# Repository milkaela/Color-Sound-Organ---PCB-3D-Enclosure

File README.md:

# Color Sound Organ: PCB-3D-Enclosure
This project contains a complete design for a **sound-reactive light organ** with 3 channels (bass, mid, treble), using a PCB designed in KiCad and a custom 3D-printed case modeled in FreeCAD.
It is intended as a simple analog project for beginners or hobbyists who want to create visual effects based on audio input.

## 📦 Files Included

| File | Description |
|------|-------------|
| `3leduri.kicad_pcb` | PCB layout for the sound organ |
| `3leduri.kicad_sch` | Schematic diagram (circuit design) |
| `3leduri.kicad_pro` | KiCad project file |
| `3leduri.kicad_prl` | Layout view settings |
| `3leduri.xml`       | Netlist and BOM data export |
| `3leduri_bom_.csv`  | Bill of materials (CSV format) |
| `3leduri_bom_.xlsx` | Bill of materials (Excel format) |
| `fp-info-cache`     | Footprint cache used by KiCad |
| `cutie2.1.FCStd`    | 3D model of the custom case (FreeCAD format) |
---

## 🧠 Functional Description

The circuit detects three different frequency bands from an audio signal (low, mid, and high), and lights up a dedicated LED for each band accordingly.

- **Low frequencies (bass)** → LED 1
- **Mid frequencies** → LED 2
- **High frequencies (treble)** → LED 3

The PCB is designed to fit perfectly into the custom enclosure, with holes for LEDs and power input.

---

## 🛠 Tools and Technologies

- **KiCad** – for PCB design
- **FreeCAD** – for designing the case
- **3D Printer** – to fabricate the enclosure
- (Optional) **Audio signal source** – via jack, aux, or microphone

---

## 🖨️ 3D Printing Information

- Format: `.FCStd` (native FreeCAD file)
- Recommended slicer: Cura, PrusaSlicer, etc.
- Material: PLA or PETG
- Print time: ~2 hours
- No supports required

---

## ⚡ Usage & Testing

1. Assemble the circuit and solder components on the PCB
2. Insert the board into the 3D-printed case
3. Connect audio input (e.g. from your phone or laptop)
4. Play music — the 3 LEDs will respond to the audio spectrum

---

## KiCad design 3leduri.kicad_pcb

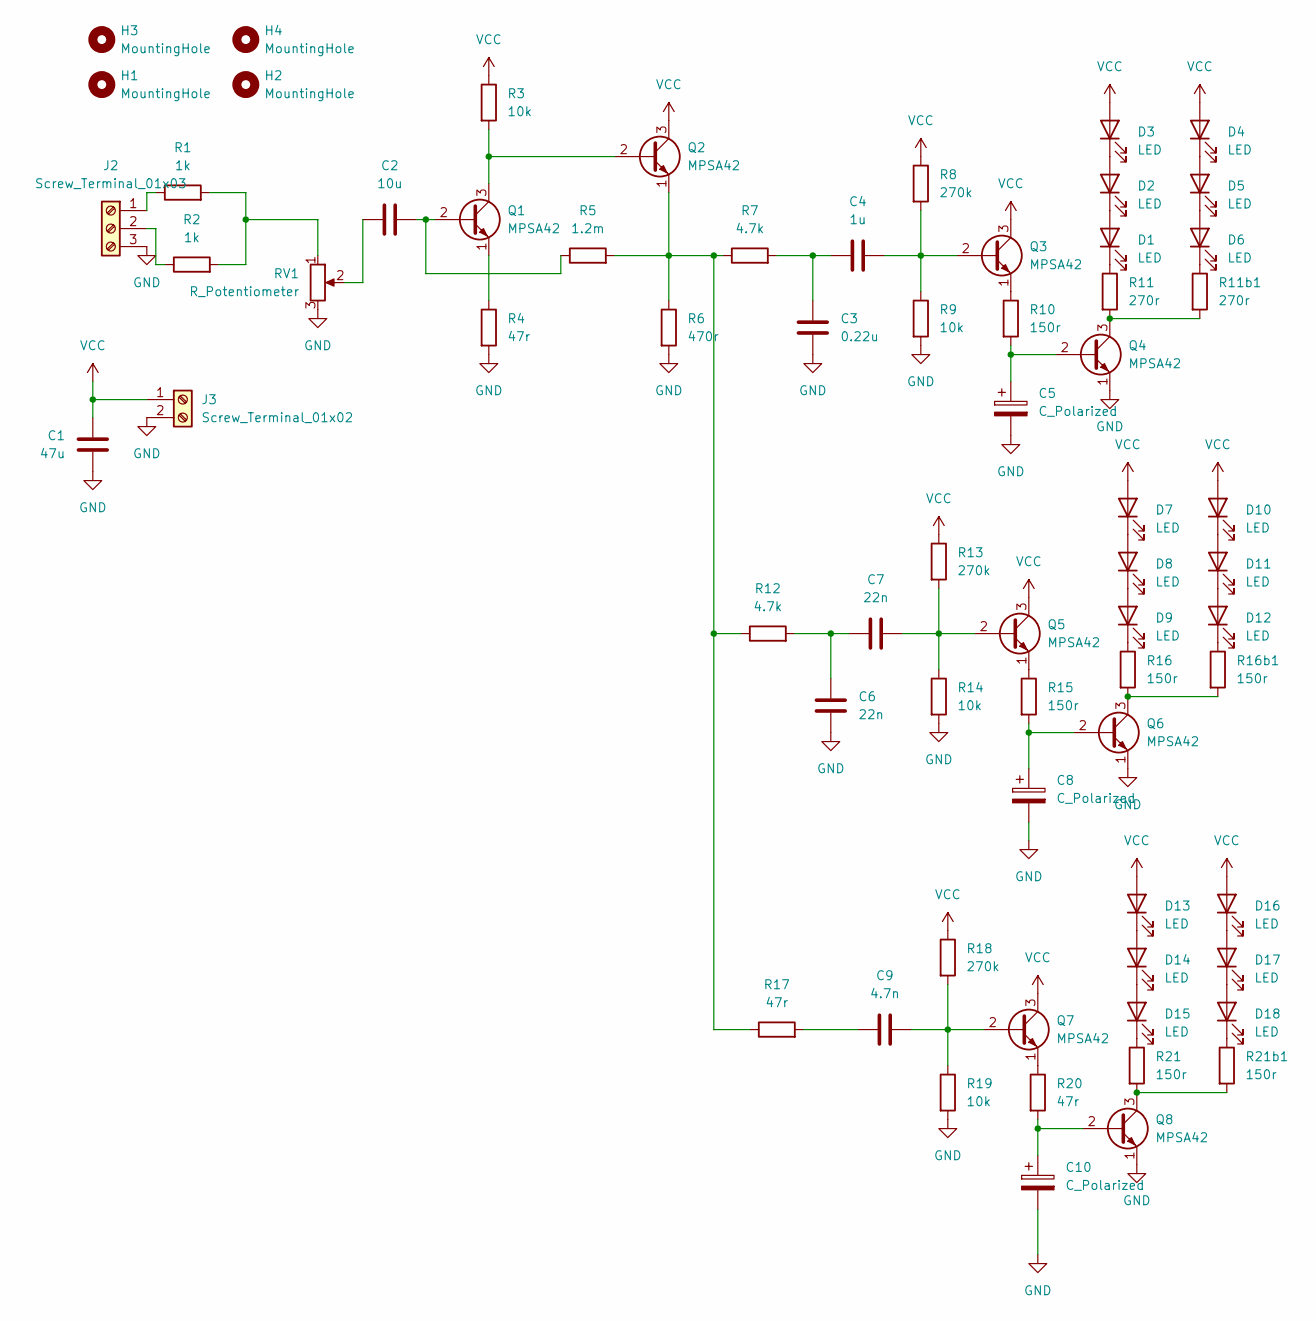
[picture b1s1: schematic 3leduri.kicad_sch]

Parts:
C1: 47u; C_1206_3216Metric_Pad1.33x1.80mm_HandSolder; mfr.part.no GCJ31CD70G476ME01L
C2: 10u; C_1206_3216Metric_Pad1.33x1.80mm_HandSolder; mfr.part.no GRM31MR61A106KE19L
C3: 0.22u; C_1206_3216Metric_Pad1.33x1.80mm_HandSolder; mfr.part.no GRM31C5C1H224JE02L
C4: 1u; C_1206_3216Metric_Pad1.33x1.80mm_HandSolder; mfr.part.no GCM31CR71H105KA55L
C5, C8, C10: C_Polarized; C_1206_3216Metric_Pad1.33x1.80mm_HandSolder
C6, C7: 22n; C_1206_3216Metric_Pad1.33x1.80mm_HandSolder; mfr.part.no GRM31BR72E223KW01L
C9: 4.7n; C_1206_3216Metric_Pad1.33x1.80mm_HandSolder; mfr.part.no GRM31CR72E473KW03L
D1, D2, D3, D4, D5, D6, D7, D8, D9, D10, D11, D12, D13, D14, D15, D16, D17, D18: LED; LED_D5.0mm; mfr.part.no MTE1201C1
H1, H2, H3, H4: MountingHole; MountingHole_3.2mm_M3
J2: Screw_Terminal_01x03; TerminalBlock_Phoenix_MKDS-1,5-3_1x03_P5.00mm_Horizontal
J3: Screw_Terminal_01x02; TerminalBlock_Phoenix_MKDS-1,5-2_1x02_P5.00mm_Horizontal; mfr.part.no 1732386
Q1, Q2, Q3, Q4, Q5, Q6, Q7, Q8: MPSA42; TO-92_Inline; mfr.part.no MPSA42
R1, R2: 1k; R_1206_3216Metric_Pad1.30x1.75mm_HandSolder; mfr.part.no RV1206JR-071KL
R3, R9, R14, R19: 10k; R_1206_3216Metric_Pad1.30x1.75mm_HandSolder; mfr.part.no ERJ-U08J103V
R4, R17, R20: 47r; R_1206_3216Metric_Pad1.30x1.75mm_HandSolder; mfr.part.no SR1206JR-1347RL
R5: 1.2m; R_1206_3216Metric_Pad1.30x1.75mm_HandSolder; mfr.part.no AC1206JR-071M2L
R6: 470r; R_1206_3216Metric_Pad1.30x1.75mm_HandSolder; mfr.part.no SR1206KR-7W470RL
R7, R12: 4.7k; R_1206_3216Metric_Pad1.30x1.75mm_HandSolder; mfr.part.no AR1206JR-074K7L
R8, R13, R18: 270k; R_1206_3216Metric_Pad1.30x1.75mm_HandSolder; mfr.part.no AF1206JR-07270KL
R10, R15, R16, R16b1, R21, R21b1: 150r; R_1206_3216Metric_Pad1.30x1.75mm_HandSolder; mfr.part.no SR1206JR-7W150RL
R11, R11b1: 270r; R_1206_3216Metric_Pad1.30x1.75mm_HandSolder; mfr.part.no RCA1206270RJNEA
RV1: R_Potentiometer; Potentiometer_Bourns_3386P_Vertical; mfr.part.no 3386P-1-564LF

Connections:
GND: C1.2, C3.2, C5.2, C6.2, C8.2, C10.2, J2.3, J3.2, Q4.1 (E), Q6.1 (E), Q8.1 (E), R4.2, R6.2, R9.2, R14.2, R19.2, RV1.3
unnamed: C2.1, RV1.2
unnamed: C3.1, C4.1, R7.2
unnamed: C6.1, C7.1, R12.2
unnamed: C9.1, R17.2
unnamed: D1.2 (A), D2.1 (K)
unnamed: D1.1 (K), R11.1
unnamed: D2.2 (A), D3.1 (K)
unnamed: D4.1 (K), D5.2 (A)
unnamed: D5.1 (K), D6.2 (A)
unnamed: D6.1 (K), R11b1.1
unnamed: D7.1 (K), D8.2 (A)
unnamed: D8.1 (K), D9.2 (A)
unnamed: D9.1 (K), R16.1
unnamed: D10.1 (K), D11.2 (A)
unnamed: D11.1 (K), D12.2 (A)
unnamed: D12.1 (K), R16b1.1
unnamed: D13.1 (K), D14.2 (A)
unnamed: D14.1 (K), D15.2 (A)
unnamed: D15.1 (K), R21.1
unnamed: D16.1 (K), D17.2 (A)
unnamed: D17.1 (K), D18.2 (A)
unnamed: D18.1 (K), R21b1.1
unnamed: J2.1, R1.1
unnamed: J2.2, R2.1
unnamed: C2.2, Q1.2 (B), R5.1
unnamed: Q1.3 (C), Q2.2 (B), R3.2
unnamed: Q1.1 (E), R4.1
unnamed: Q2.1 (E), R5.2, R6.1, R7.1, R12.1, R17.1
unnamed: C4.2, Q3.2 (B), R8.2, R9.1
unnamed: Q3.1 (E), R10.1
unnamed: C5.1, Q4.2 (B), R10.2
unnamed: Q4.3 (C), R11.2, R11b1.2
unnamed: C7.2, Q5.2 (B), R13.2, R14.1
unnamed: Q5.1 (E), R15.1
unnamed: C8.1, Q6.2 (B), R15.2
unnamed: Q6.3 (C), R16.2, R16b1.2
unnamed: C9.2, Q7.2 (B), R18.2, R19.1
unnamed: Q7.1 (E), R20.1
unnamed: C10.1, Q8.2 (B), R20.2
unnamed: Q8.3 (C), R21.2, R21b1.2
unnamed: R1.2, R2.2, RV1.1
VCC: C1.1, D3.2 (A), D4.2 (A), D7.2 (A), D10.2 (A), D13.2 (A), D16.2 (A), J3.1, Q2.3 (C), Q3.3 (C), Q5.3 (C), Q7.3 (C), R3.1, R8.1, R13.1, R18.1

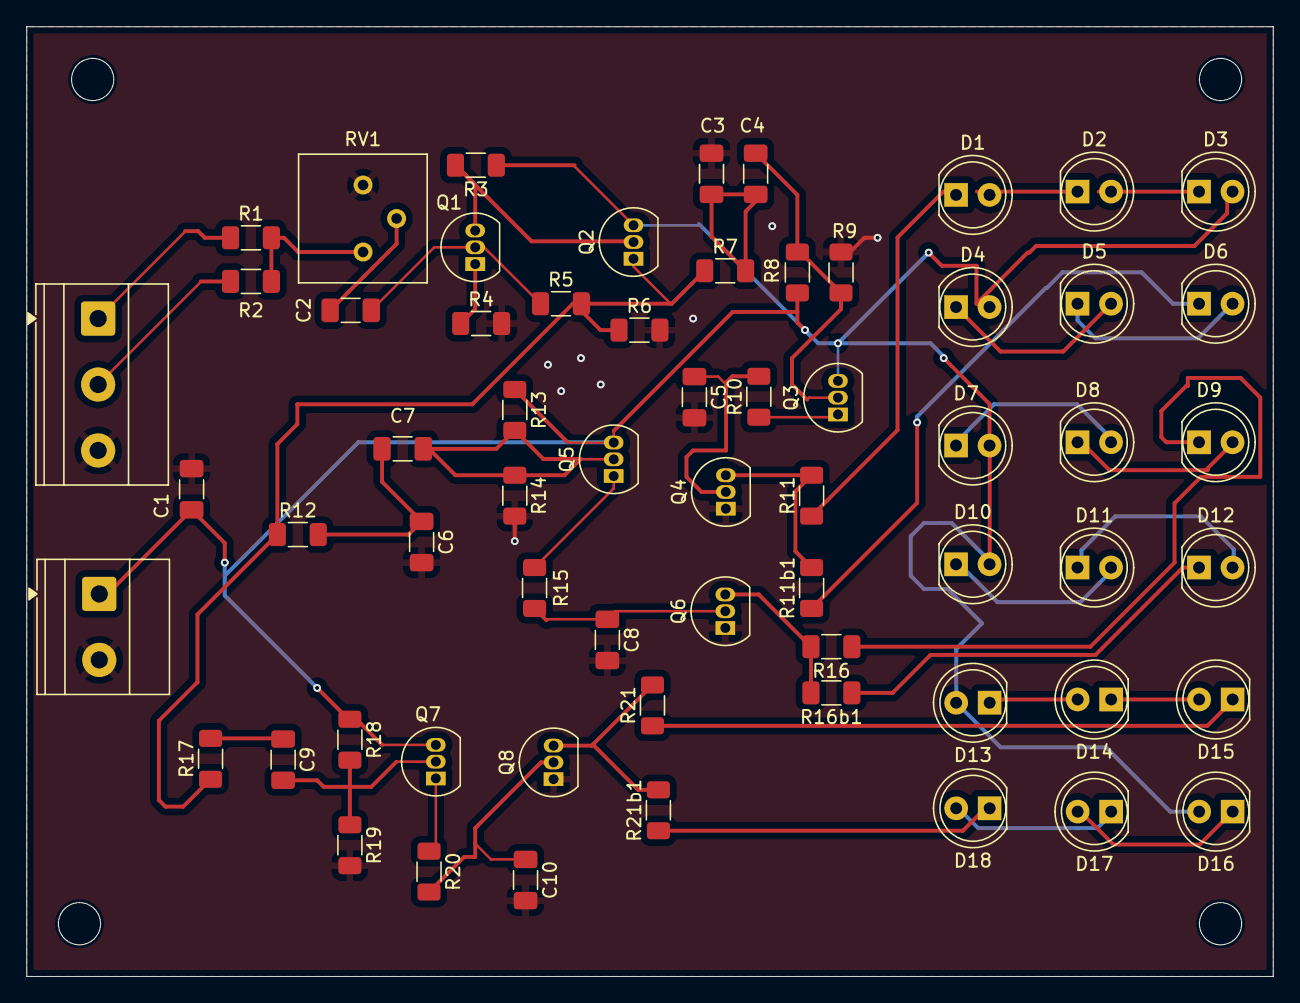
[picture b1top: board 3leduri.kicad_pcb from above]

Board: 2 copper layers, 94.5 x 72.0 mm, 67 parts (0 on the bottom side), 43 nets.

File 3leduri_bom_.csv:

Component,Description,Part,References,Value,Footprint,Quantity Per PCB,Datasheet,mfr.part.no,sup.ref,Sim.Pins
1,Unpolarized capacitor,C,C9,4.7n,C_1206_3216Metric_Pad1.33x1.80mm_HandSolder,1,~,GRM31CR72E473KW03L,https://ro.mouser.com/ProductDetail/Murata-Electronics/GRM31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,
2,Unpolarized capacitor,C,C6 C7,22n,C_1206_3216Metric_Pad1.33x1.80mm_HandSolder,2,~,GRM31BR72E223KW01L,http://ro.mouser.com/ProductDetail/Murata-Electronics/GRM31B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,
3,Unpolarized capacitor,C,C3,0.22u,C_1206_3216Metric_Pad1.33x1.80mm_HandSolder,1,~,GRM31C5C1H224JE02L,https://ro.mouser.com/ProductDetail/Murata-Electronics/GRM31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,
4,Unpolarized capacitor,C,C4,1u,C_1206_3216Metric_Pad1.33x1.80mm_HandSolder,1,~,GCM31CR71H105KA55L,https://ro.mouser.com/ProductDetail/Murata-Electronics/GCM31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,
5,Unpolarized capacitor,C,C5 C8 C10,4.7u,C_1206_3216Metric_Pad1.33x1.80mm_HandSolder,3,~,GCM31CC71H475MA03K,https://ro.mouser.com/ProductDetail/Murata-Electronics/GCM31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,
6,Unpolarized capacitor,C,C2,10u,C_1206_3216Metric_Pad1.33x1.80mm_HandSolder,1,~,GRM31MR61A106KE19L,https://ro.mouser.com/ProductDetail/Murata-Electronics/GRM31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,
7,Unpolarized capacitor,C,C1,47u,C_1206_3216Metric_Pad1.33x1.80mm_HandSolder,1,~,GCJ31CD70G476ME01L,https://ro.mouser.com/ProductDetail/Murata-Electronics/GCJ31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,
8,Light emitting diode,LED,D1 D2 D3 D4 D5 D6 D7 D8 D9 D10 D11 D12 D13 D14 D15 D16 D17 D18,LED,LED_D5.0mm,18,~,MTE1201C1,https://ro.mouser.com/ProductDetail/Marktech-Optoelectronics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,1=K 2=A
9,"Generic screw terminal, single row, 01x02, script generated (kicad-library-utils/schlib/autogen/connector/)",Screw_Terminal_01x02,J1 J3,Screw_Terminal_01x02,"TerminalBlock_Phoenix_MKDS-1,5-2_1x02_P5.00mm_Horizontal",2,~,1732386,https://ro.mouser.com/ProductDetail/Phoenix-Contact/1732386?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,
10,"0.5A Ic, 300V Vce, NPN High Voltage Transistor, TO-92",MPSA42,Q1 Q2 Q3 Q4 Q5 Q6 Q7 Q8,MPSA42,TO-92_Inline,8,http://www.onsemi.com/pub_link/Collateral/MPSA42-D.PDF,MPSA42,https://ro.mouser.com/ProductDetail/onsemi-Fairchild/MPSA42?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,
11,Resistor,R,R5,1.2m,R_1206_3216Metric_Pad1.30x1.75mm_HandSolder,1,~,AC1206JR-071M2L,https://ro.mouser.com/ProductDetail/YAGEO/SR1206JR-1347RL?qs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,
12,Resistor,R,R4 R17 R20,47r,R_1206_3216Metric_Pad1.30x1.75mm_HandSolder,3,~,SR1206JR-1347RL,https://ro.mouser.com/ProductDetail/TE-Connectivity-Neohm/EP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,
13,Resistor,R,R10 R15 R16 R16b1 R21 R21b1,150r,R_1206_3216Metric_Pad1.30x1.75mm_HandSolder,6,~,SR1206JR-7W150RL,https://ro.mouser.com/ProductDetail/YAGEO/SR1206JR-7W150RL?q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,
14,Resistor,R,R11 R11b1,270r,R_1206_3216Metric_Pad1.30x1.75mm_HandSolder,2,~,RCA1206270RJNEA,https://ro.mouser.com/ProductDetail/Vishay/RCA1206270RJNEA?q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,
15,Resistor,R,R6,470r,R_1206_3216Metric_Pad1.30x1.75mm_HandSolder,1,~,SR1206KR-7W470RL,https://ro.mouser.com/ProductDetail/YAGEO/SR1206KR-7W470RL?q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,
16,Resistor,R,R1 R2,1k,R_1206_3216Metric_Pad1.30x1.75mm_HandSolder,2,~,RV1206JR-071KL,https://ro.mouser.com/ProductDetail/YAGEO/RV1206JR-071KL?qs=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,
17,Resistor,R,R7 R12,4.7k,R_1206_3216Metric_Pad1.30x1.75mm_HandSolder,2,~,AR1206JR-074K7L,https://ro.mouser.com/ProductDetail/YAGEO/AR1206JR-074K7L?qs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,
18,Resistor,R,R3 R9 R14 R19,10k,R_1206_3216Metric_Pad1.30x1.75mm_HandSolder,4,~,ERJ-U08J103V,https://ro.mouser.com/ProductDetail/Panasonic/ERJ-U08J103V?q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,
19,Resistor,R,R8 R13 R18,270k,R_1206_3216Metric_Pad1.30x1.75mm_HandSolder,3,~,AF1206JR-07270KL,https://ro.mouser.com/ProductDetail/YAGEO/AF1206JR-07270KL?q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,
20,Potentiometer,R_Potentiometer,RV1,R_Potentiometer,Potentiometer_Bourns_3386P_Vertical,1,~,3386P-1-564LF,https://ro.mouser.com/ProductDetail/Bourns/3386P-1-564LF?qs=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,





Component Groups:,20
Component Count:,63
Fitted Components:,63
Number of PCBs:,1
Total components:,63
Schematic Version:,
Schematic Date:,
PCB Variant:,default
BoM Date:,2025-07-24T14:40:16+0300
Schematic Source:,3leduri.kicad_sch
KiCad Version:,Eeschema 9.0.3
